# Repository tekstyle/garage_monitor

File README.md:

garage_monitor
==============

Monitor garage door and close it if left open after a certain amount of time.

This is my first attempt at this program. I'm sure there is a more efficient way to doing this. If you have any suggestions please share them with me. 

Thanks

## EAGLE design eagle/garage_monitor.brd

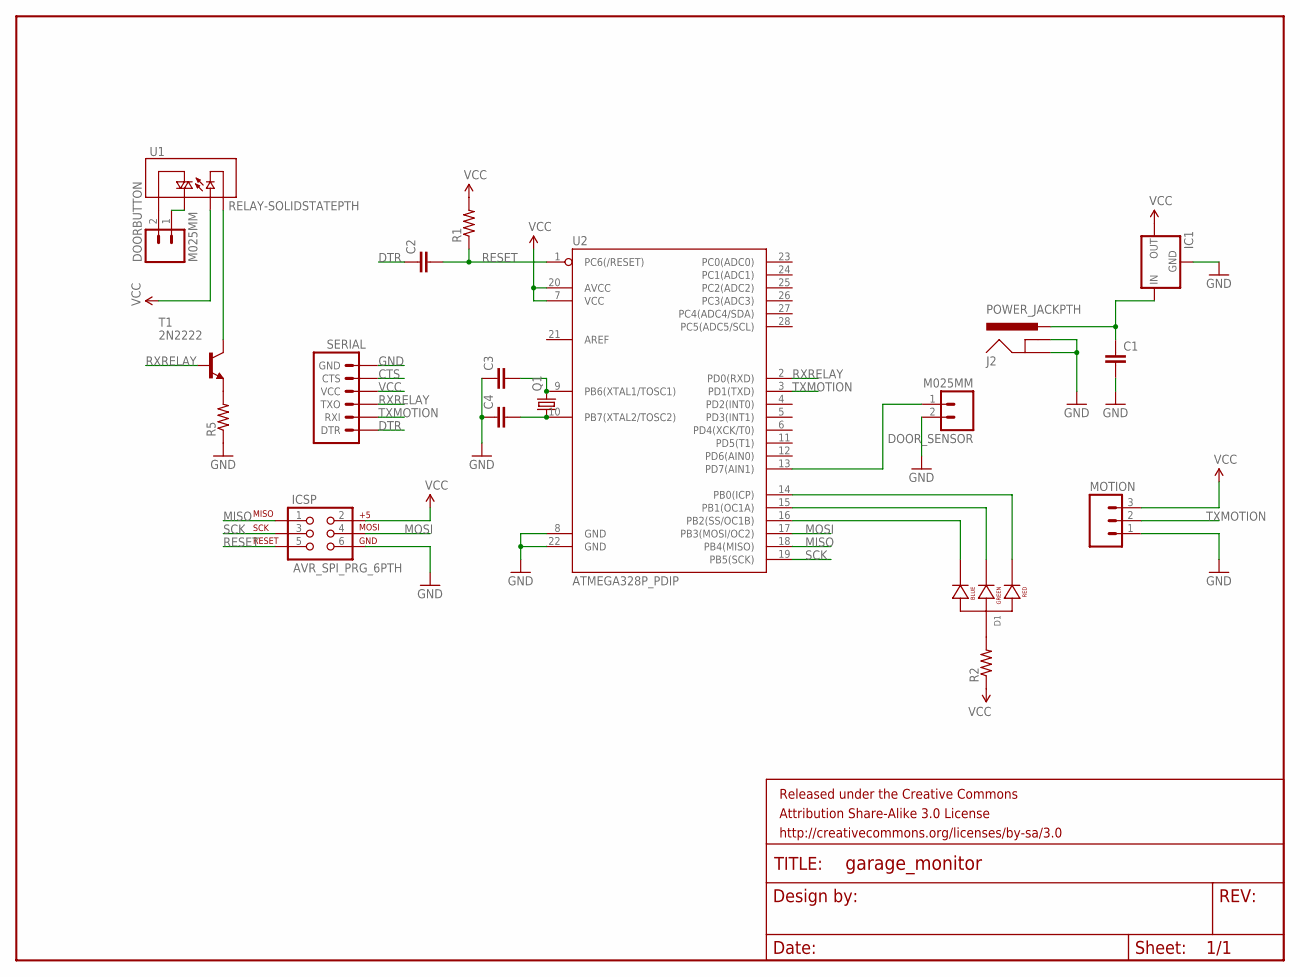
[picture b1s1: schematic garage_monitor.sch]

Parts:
C1, C2: CAPPTH; CAP-PTH-SMALL
C3, C4: CAPEZ; CAP-PTH-SMALLEZ
D1: LED-RGB-CA-THRUCLEAR; LED-RGB-THRU
DOORBUTTON: M025MM; SCREWTERMINAL-5MM-2
DOOR_SENSOR: M025MM; SCREWTERMINAL-5MM-2
FRAME1: FRAME-LETTER; CREATIVE_COMMONS
IC1: V_REG_78XXSIDE; 78XXL
ICSP: AVR_SPI_PRG_6PTH; 2X3
J2: POWER_JACKPTH; POWER_JACK_PTH
MOTION: M03PTH; 1X03
Q1: CRYSTALHC49S; HC49/S
R1, R2, R5: RESISTORPTH-1/4W; AXIAL-0.4
SERIAL: ARDUINO_SERIAL_PROGRAMPTH; 1X06
T1: 2N2222; TO18
U1: RELAY-SOLIDSTATEPTH; RELAY-S108T02
U2: ATMEGA328P_PDIP; DIL28-3

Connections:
CTS: SERIAL.5 (CTS)
DTR: C2.1, SERIAL.1 (DTR)
GND: C1.2, C3.1, C4.1, DOOR_SENSOR.2, IC1.GND, ICSP.6, J2.GND, J2.GNDBREAK, MOTION.1, R5.P$1 (1), SERIAL.6 (GND), U2.8 (GND), U2.22 (GND)
MISO: ICSP.1, U2.18 (PB4(MISO))
MOSI: ICSP.4, U2.17 (PB3(MOSI/OC2))
unnamed: DOOR_SENSOR.1, U2.13 (PD7(AIN1))
unnamed: R5.P$2 (2), T1.1 (E)
unnamed: T1.3 (C), U1.4 (-)
unnamed: D1.2 (ANODE), R2.P$2 (2)
unnamed: C3.2, Q1.2, U2.9 (PB6(XTAL1/TOSC1))
unnamed: C4.2, Q1.1, U2.10 (PB7(XTAL2/TOSC2))
unnamed: D1.4 (BLUE_CATHODE), U2.16 (PB2(SS/OC1B))
unnamed: D1.3 (GREEN_CATHODE), U2.15 (PB1(OC1A))
unnamed: D1.1 (RED_CATHODE), U2.14 (PB0(ICP))
unnamed: DOORBUTTON.2, U1.1 (T1)
unnamed: DOORBUTTON.1, U1.2 (T2)
unnamed: C1.1, IC1.IN, J2.PWR
RESET: C2.2, ICSP.5, R1.P$1 (1), U2.1 (PC6(/RESET))
RXRELAY: SERIAL.3 (TXO), T1.2 (B), U2.2 (PD0(RXD))
SCK: ICSP.3, U2.19 (PB5(SCK))
TXMOTION: MOTION.2, SERIAL.2 (RXI), U2.3 (PD1(TXD))
VCC: IC1.OUT, ICSP.2, MOTION.3, R1.P$2 (2), R2.P$1 (1), SERIAL.4 (VCC), U1.3 (+), U2.7 (VCC), U2.20 (AVCC)

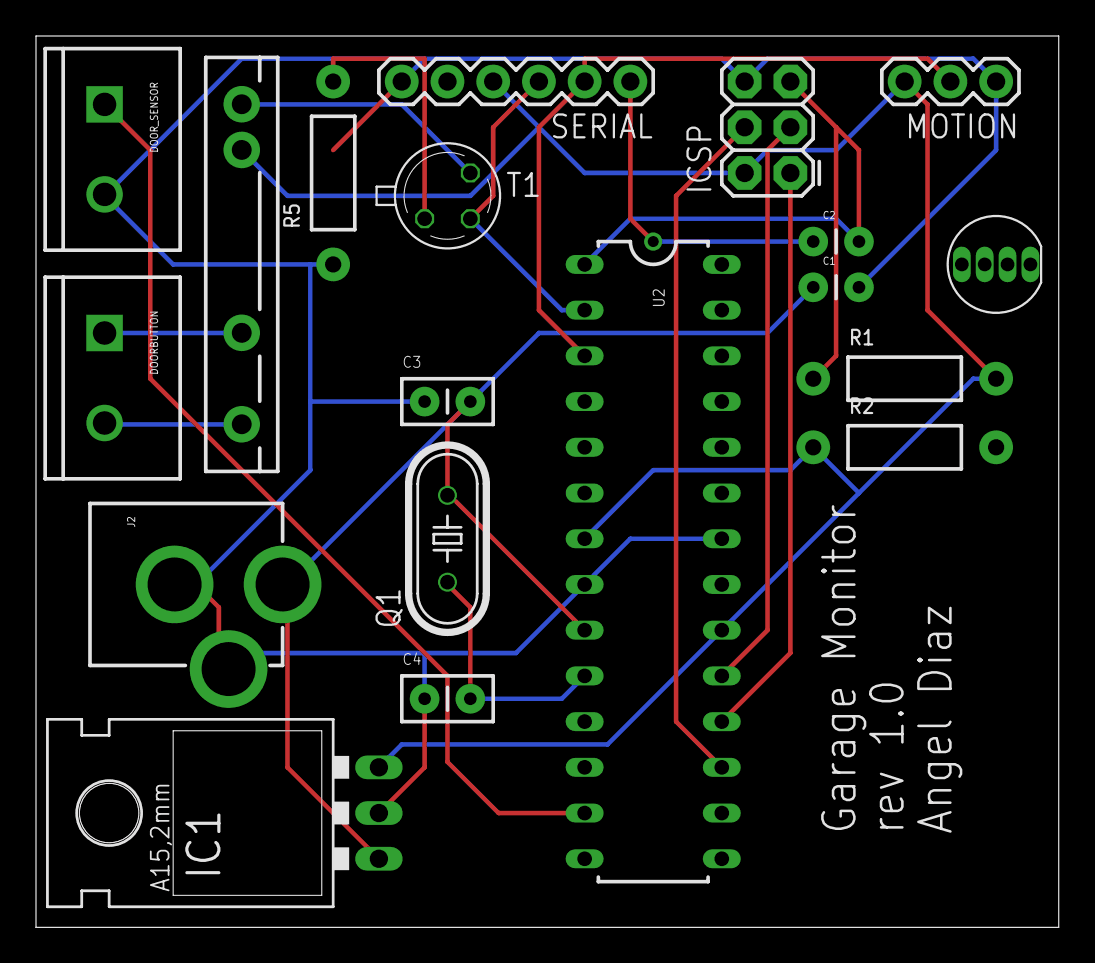
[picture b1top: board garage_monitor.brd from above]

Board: 2 copper layers, 56.8 x 49.5 mm, 20 parts (0 on the bottom side), 21 nets.

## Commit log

2014-01-16 Initial source code commit
2014-01-18 removed old code and added comments.
2014-01-18 added lcd
2014-01-19 added eagle files
2014-01-19 updated eagle schematic

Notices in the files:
parts and their libraries:
SparkFun-Resistors: Licensing: CC v3.0 Share-Alike You are welcome to use this library for commercial purposes.
SparkFun-Aesthetics: Released under the Creative Commons Attribution Share-Alike 3.0 License
SparkFun-Aesthetics: http://creativecommons.org/licenses/by-sa/3.0
